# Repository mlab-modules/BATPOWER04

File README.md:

# BATPOWER04 - Step-down Voltage Converter Module

BATPOWER04 is a step-down voltage converter module based on the [LM3485](doc/pdf/lm3485.pdf) PFET buck controller. The input voltage range is 4.5 V to 16 V. The output voltage can be selected by jumpers as 3.3 V or 5 V, or configured as a custom voltage using an external resistor or trimmer. The output voltage range is 0.25 V to Vin.

The module is especially suited for battery-powered applications, but it can also be used as a step-down converter from an external 12 V supply to 3.3 V or 5 V for MLAB designs. Its key feature is high efficiency, up to 93%, which helps reduce waste heat.

| Parameter | Value | Description |
|-----------|-------|-------------|
| Step-down controller | [LM3485](doc/pdf/lm3485.pdf) | PFET Buck controller |
| Vin | 4.5 V - 16 V | Input voltage range |
| Vout | 0.25 V - Vin | 3.3 V or 5 V selectable by jumper. Other values require an external resistor or trimmer. |

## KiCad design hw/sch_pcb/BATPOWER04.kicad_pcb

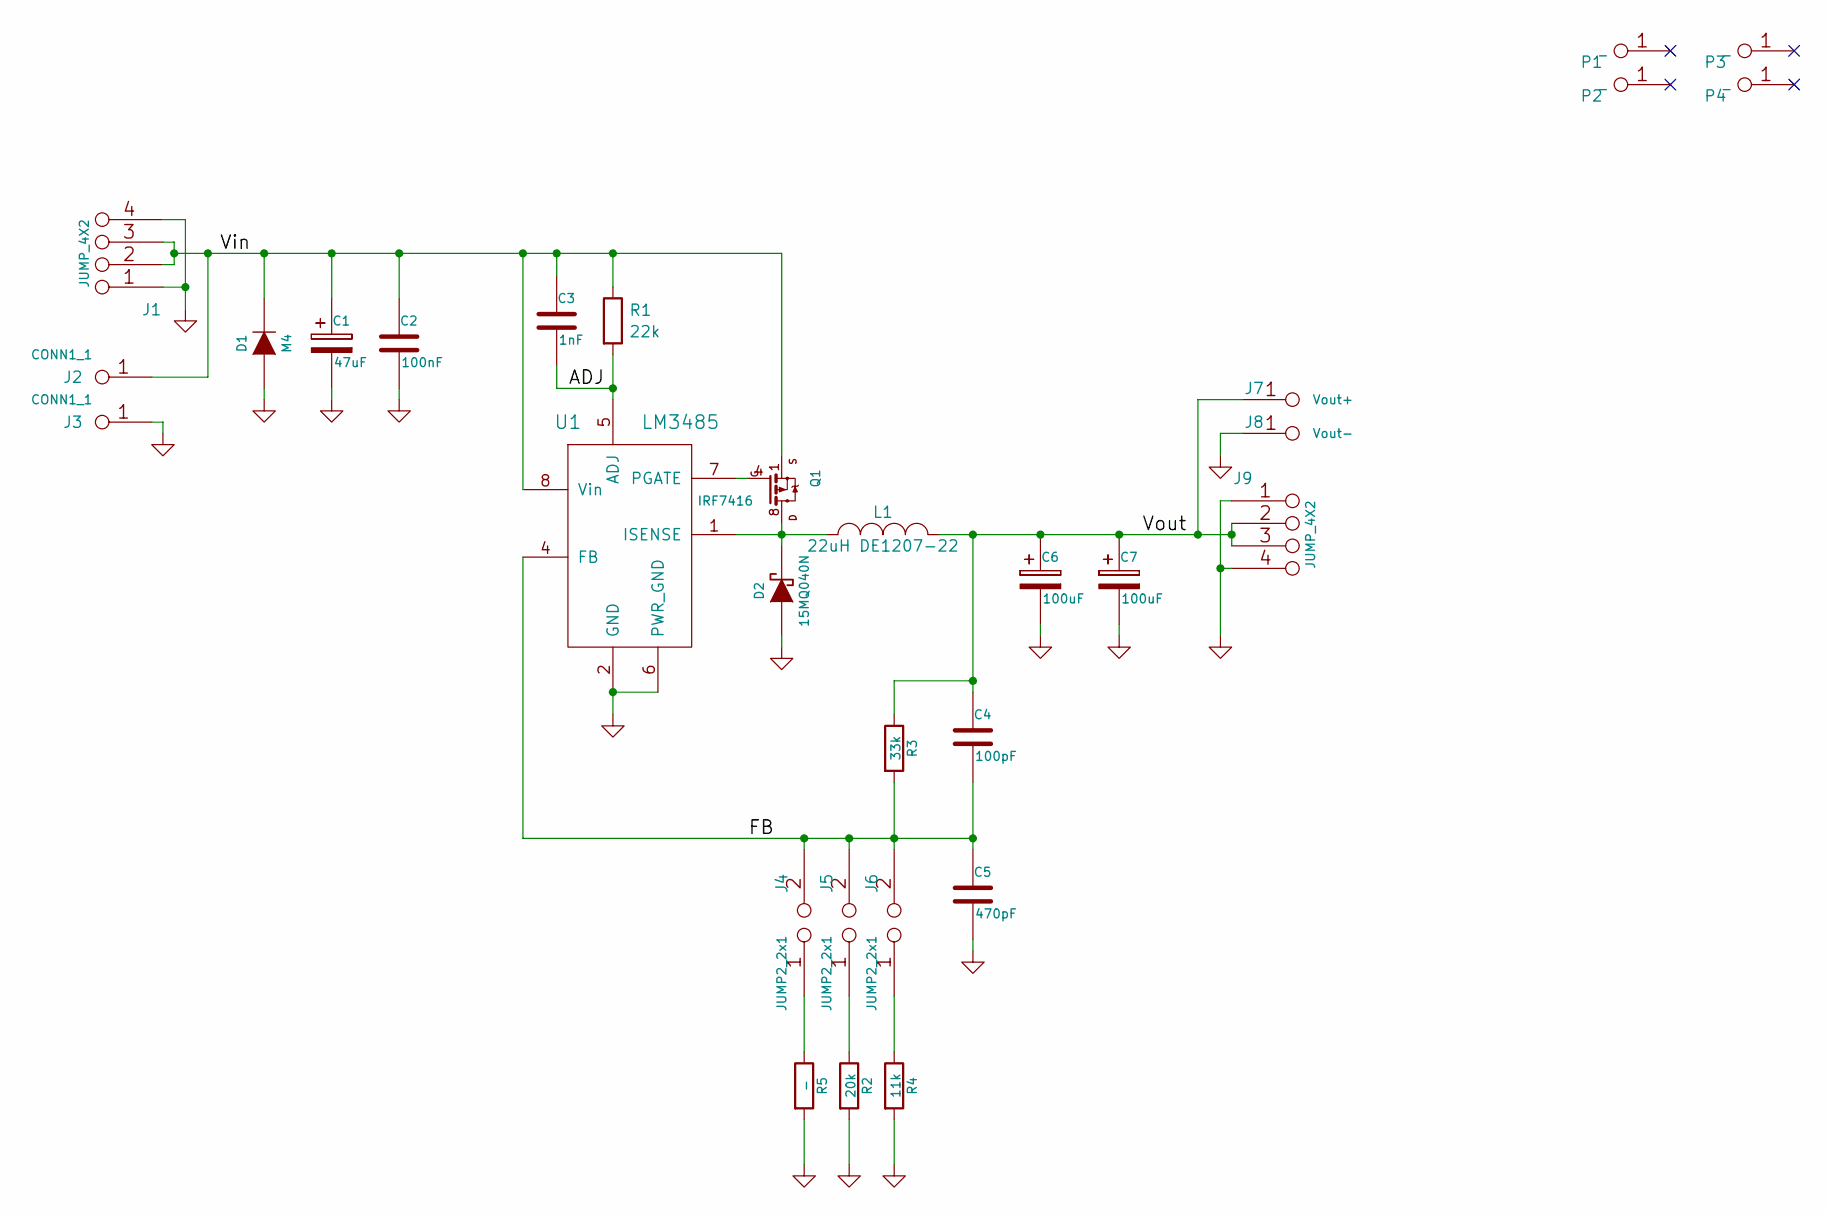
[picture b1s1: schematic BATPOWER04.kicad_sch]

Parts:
C1: 47uF; TantalC_SizeC_Reflow
C2: 100nF; SMD-0805
C3: 1nF; SMD-0805
C4: 100pF; SMD-0805
C5: 470pF; SMD-0805
C6, C7: 100uF; TantalC_SizeD_Reflow
D1: M4; Diode-SMA_Standard
D2: 15MQ040N; Diode-SMA_Standard
J1, J9: JUMP_4X2; Pin_Header_Straight_2x04
J2, J3: CONN1_1; WAGO256
J4, J5, J6: JUMP2_2x1; Pin_Header_Straight_1x02
J7: Vout+; WAGO256
J8: Vout-; WAGO256
L1: 22uH DE1207-22; DE1205-10
P1, P2, P3, P4: _; MountingHole_3mm
Q1: IRF7416; SO-8
R1: 22k; SMD-0805
R2: 20k; SMD-0805
R3: 33k; SMD-0805
R4: 11k; SMD-0805
R5: -; SMD-0805
U1: LM3485; MSOP-8_3x3mm_Pitch0.65mm

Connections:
/ADJ: C3.2, R1.2, U1.5 (ADJ)
/FB: C4.2, C5.1, J4.2, J5.2, J6.2, R3.2, U1.4 (FB)
/Vin: C1.1, C2.1, C3.1, D1.2 (K), J1.2, J1.3, J1.6, J1.7, J2.1, Q1.1 (S), Q1.2 (S), Q1.3 (S), R1.1, U1.8 (Vin)
/Vout: C4.1, C6.1, C7.1, J7.1, J9.2, J9.3, J9.6, J9.7, L1.2, R3.1
GND: C1.2, C2.2, C5.2, C6.2, C7.2, D1.1 (A), D2.1 (A), J1.1, J1.4, J1.5, J1.8, J3.1, J8.1, J9.1, J9.4, J9.5, J9.8, R2.2, R4.2, R5.2, U1.2 (GND), U1.6 (PWR_GND)
unnamed: D2.2 (K), L1.1, Q1.5 (D), Q1.6 (D), Q1.7 (D), Q1.8 (D), U1.1 (ISENSE)
unnamed: J4.1, R5.1
unnamed: J5.1, R2.1
unnamed: J6.1, R4.1
unnamed: Q1.4 (G), U1.7 (PGATE)

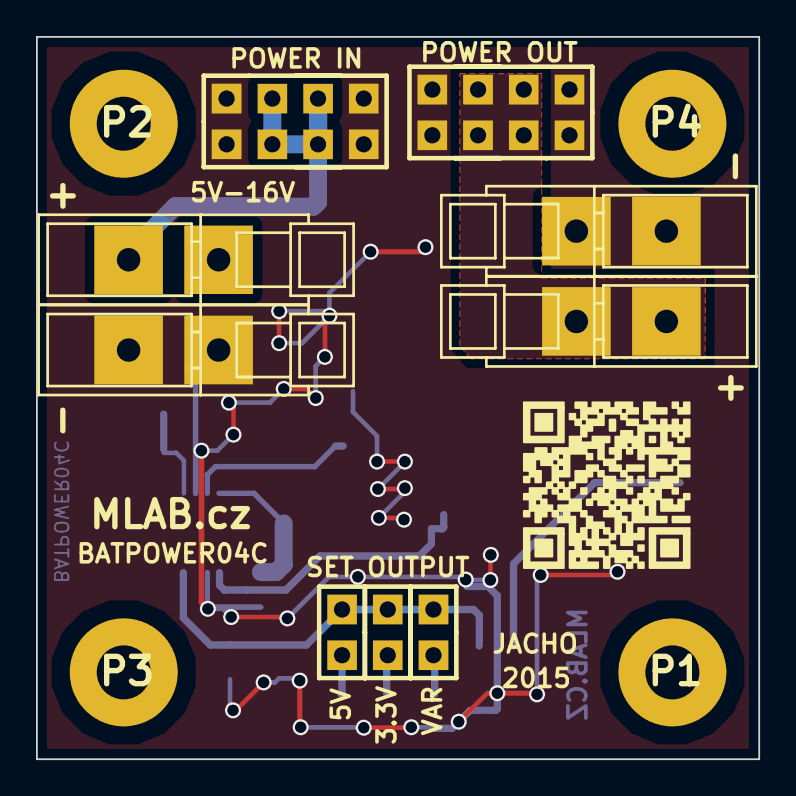
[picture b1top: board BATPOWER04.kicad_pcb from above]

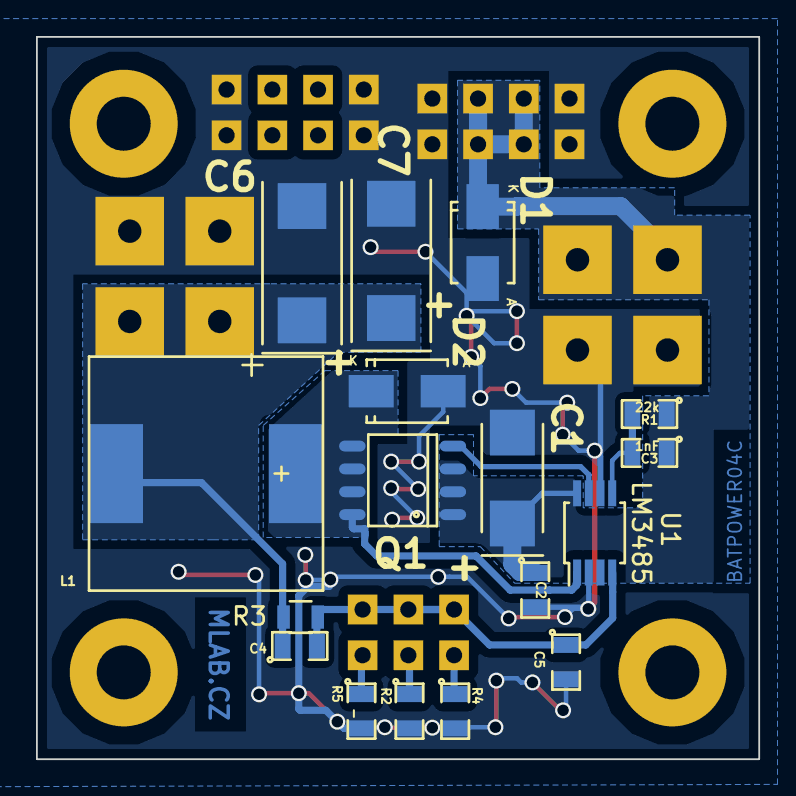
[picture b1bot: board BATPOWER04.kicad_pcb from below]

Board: 2 copper layers, 40.1 x 40.1 mm, 30 parts (17 on the bottom side), 10 nets.

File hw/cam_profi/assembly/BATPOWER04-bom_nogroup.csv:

Component,Description,Part,References,Value,Footprint,Quantity Per PCB,Datasheet
1,,C_7,C4,100pF,SMD-0805,1,
2,,C_8,C5,470pF,SMD-0805,1,
3,,C_5,C3,1nF,SMD-0805,1,
4,,C_6,C2,100nF,SMD-0805,1,
5,,CP2_4,C1,47uF,TantalC_SizeC_Reflow,1,
6,,CP2_5,C6,100uF,TantalC_SizeD_Reflow,1,
7,,CP2_6,C7,100uF,TantalC_SizeD_Reflow,1,
8,,DIODESCH_2,D2,15MQ040N,Diode-SMA_Standard,1,
9,,DIODE_2,D1,M4,Diode-SMA_Standard,1,
10,,CONN1_1_5,J2,CONN1_1,WAGO256,1,
11,,CONN1_1_6,J3,CONN1_1,WAGO256,1,
12,,JUMP2_2x1_4,J4,JUMP2_2x1,Pin_Header_Straight_1x02,1,
13,,JUMP2_2x1_5,J5,JUMP2_2x1,Pin_Header_Straight_1x02,1,
14,,JUMP2_2x1_6,J6,JUMP2_2x1,Pin_Header_Straight_1x02,1,
15,,JUMP_4X2_3,J1,JUMP_4X2,Pin_Header_Straight_2x04,1,
16,,JUMP_4X2_4,J9,JUMP_4X2,Pin_Header_Straight_2x04,1,
17,,CONN1_1_8,J7,Vout+,WAGO256,1,
18,,CONN1_1_7,J8,Vout-,WAGO256,1,
19,,INDUCTOR_SMALL_2,L1,22uH DE1207-22,DE1205-10,1,
20,,IRF7416_2,Q1,IRF7416,SO-8,1,
21,Resistor,R,R4,11k,SMD-0805,1,~
22,Resistor,R,R2,20k,SMD-0805,1,~
23,Resistor,R,R1,22k,SMD-0805,1,~
24,Resistor,R,R3,33k,SMD-0805,1,~
25,Resistor,R,R5,-,SMD-0805,1,~
26,,LM3485_2,U1,LM3485,MSOP-8_3x3mm_Pitch0.65mm,1,

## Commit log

2017-08-22 rename category folders
2017-08-22 rename files and module folders
2017-08-22 change images path
2017-08-22 create hw folder
2017-08-22 change filepaths
2017-08-22 rm empty json html files, rename module.json files
2017-08-22 new .json files
2017-11-03 [MLABweb] 2017-11-03 09:25:40 BATPOWER04C
2017-11-16 [MLABweb] 2017-11-16 10:44:17 BATPOWER04A
2017-11-16 [MLABweb] 2017-11-16 10:44:30 BATPOWER04B
2018-04-12 [MLABweb] Documentaion edits; BATPOWER04B
2018-11-05 Presun obrazku do slozky img. Pregenerovani dokumentaci.
2019-01-09 [MLABweb] new image
2022-04-06 automated commit; add github actions
2022-04-06 Update actions products
2023-05-25 Update metadata files
2023-05-28 Update workflow files
2023-07-05 automated commit; rename source files to new naming convence
2023-09-16 Update image to image_title
2023-09-16 Update status
2026-05-11 Update assets submodule.
2026-05-12 Update project to KiCADv9.
2026-05-12 Automatic update of KiCAD outputs
